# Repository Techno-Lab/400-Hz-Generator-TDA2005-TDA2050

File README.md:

# 400-Hz-Generator-TDA2005-TDA2050

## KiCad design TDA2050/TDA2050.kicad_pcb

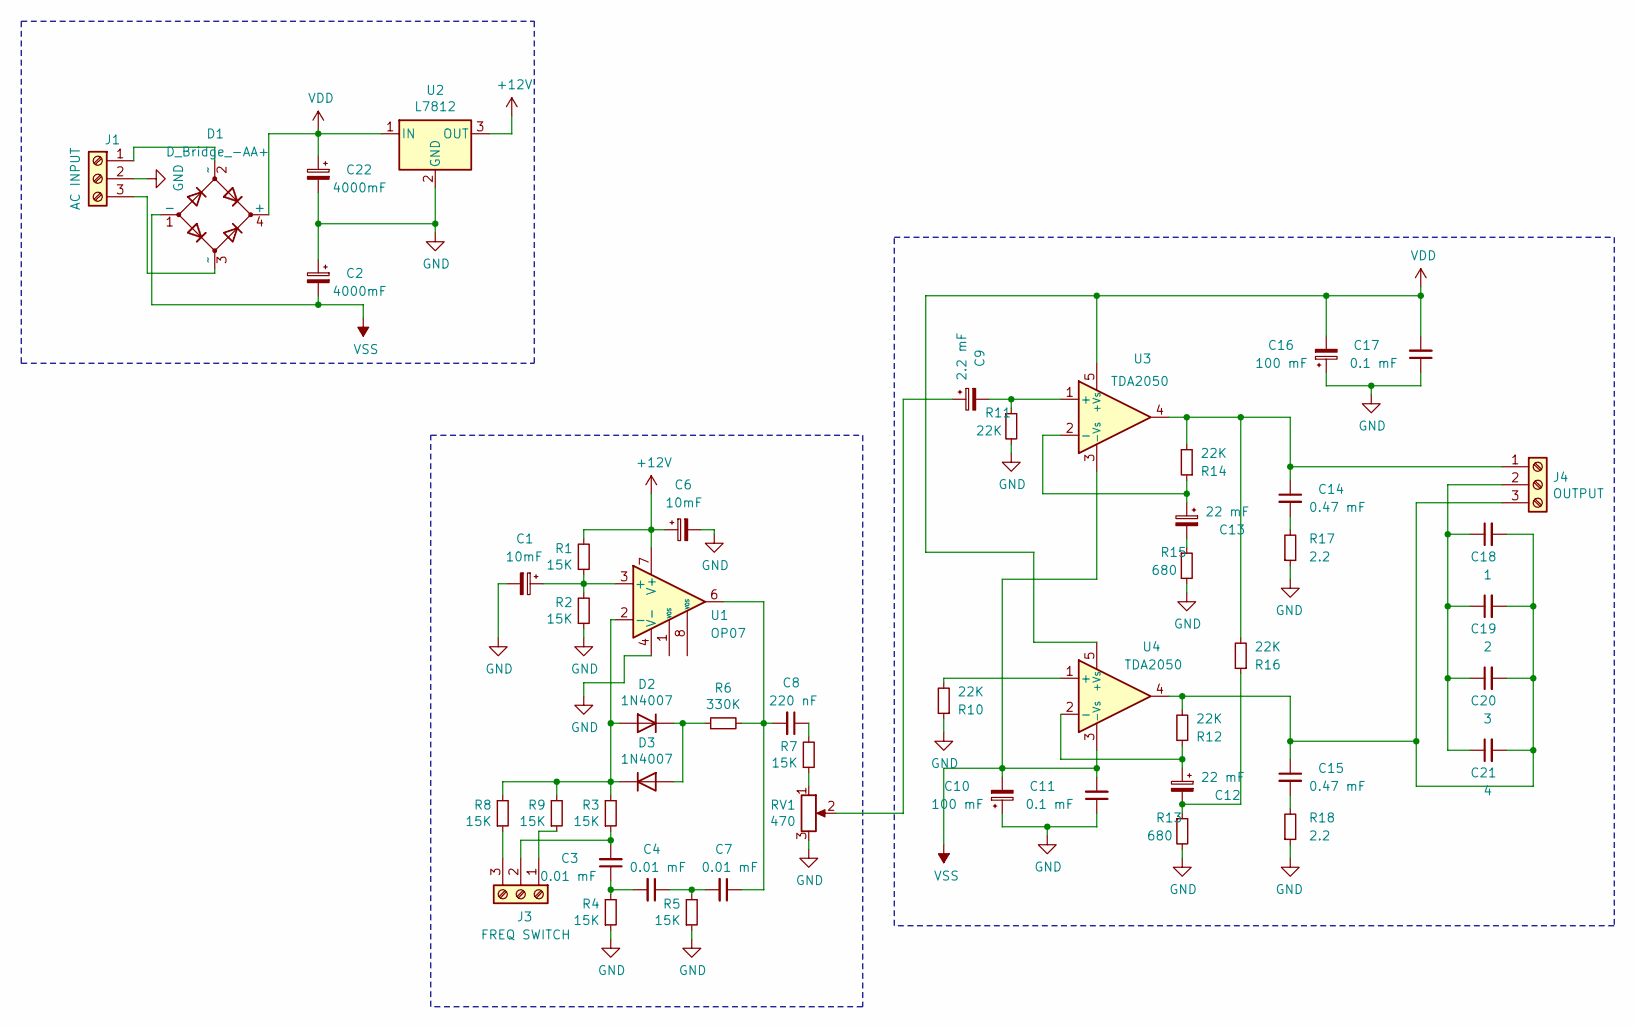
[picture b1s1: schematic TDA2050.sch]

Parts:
C1, C6: 10mF; CP_Radial_D5.0mm_P2.00mm
C2, C22: 4000mF; CP_Radial_D22.0mm_P10.00mm_SnapIn
C3, C4, C7: 0.01 mF; C_Disc_D7.5mm_W2.5mm_P5.00mm
C8: 220 nF; C_Disc_D7.5mm_W2.5mm_P5.00mm
C9: 2.2 mF; CP_Radial_D5.0mm_P2.00mm
C10, C16: 100 mF; CP_Radial_D5.0mm_P2.50mm
C11, C17: 0.1 mF; C_Disc_D7.5mm_W2.5mm_P5.00mm
C12: 22 mF; CP_Radial_D5.0mm_P2.50mm
C13: 22 mF; CP_Radial_D5.0mm_P2.00mm
C14, C15: 0.47 mF; C_Disc_D7.5mm_W2.5mm_P5.00mm
C18: 1; TerminalBlock_bornier-2_P5.08mm
C19: 2; TerminalBlock_bornier-2_P5.08mm
C20: 3; TerminalBlock_bornier-2_P5.08mm
C21: 4; TerminalBlock_bornier-2_P5.08mm
D1: D_Bridge_-AA+; Diode_Bridge_19.0x3.5x10.0mm_P5.0mm
D2, D3: 1N4007; D_DO-41_SOD81_P7.62mm_Horizontal
J1: AC INPUT; TerminalBlock_bornier-3_P5.08mm
J3: FREQ SWITCH; TerminalBlock_bornier-3_P5.08mm
J4: OUTPUT; TerminalBlock_bornier-3_P5.08mm
R1, R2, R3, R4, R5, R7, R8, R9: 15K; R_Axial_DIN0207_L6.3mm_D2.5mm_P10.16mm_Horizontal
R6: 330K; R_Axial_DIN0207_L6.3mm_D2.5mm_P10.16mm_Horizontal
R10, R11, R12, R14, R16: 22K; R_Axial_DIN0207_L6.3mm_D2.5mm_P10.16mm_Horizontal
R13, R15: 680; R_Axial_DIN0207_L6.3mm_D2.5mm_P10.16mm_Horizontal
R17, R18: 2.2; R_Axial_DIN0207_L6.3mm_D2.5mm_P10.16mm_Horizontal
RV1: 470; Potentiometer_Bourns_3296W_Vertical
U1: OP07; DIP-8_W7.62mm
U2: L7812; TO-220-3_Vertical
U3, U4: TDA2050; TO-220-5_P3.4x3.7mm_StaggerOdd_Lead3.8mm_Vertical

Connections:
+12V: C6.1, R1.2, U1.7 (V+), U2.3 (OUT)
GND: C1.2, C2.1, C6.2, C10.1, C11.1, C16.1, C17.1, C22.2, J1.2, R2.1, R4.1, R5.1, R10.1, R11.2, R13.2, R15.2, R17.1, R18.1, RV1.3, U1.4 (V-), U2.2 (GND)
unnamed: C1.1, R1.1, R2.2, U1.3 (+)
unnamed: C3.1, C4.2, R4.2
unnamed: C3.2, J3.2, R3.1
unnamed: C4.1, C7.2, R5.2
unnamed: C7.1, C8.2, R6.2, U1.6
unnamed: C8.1, R7.2
unnamed: C9.1, RV1.2
unnamed: C9.2, R11.1, U3.1 (+)
unnamed: C12.1, R12.1, U4.2 (-)
unnamed: C12.2, R13.1, R16.1
unnamed: C13.1, R14.1, U3.2 (-)
unnamed: C13.2, R15.1
unnamed: C14.1, J4.1, R14.2, R16.2, U3.4
unnamed: C14.2, R17.2
unnamed: C15.1, C18.2, C19.2, C20.2, C21.2, J4.3, R12.2, U4.4
unnamed: C15.2, R18.2
unnamed: C18.1, C19.1, C20.1, C21.1, J4.2
unnamed: D1.2 (~~), J1.1
unnamed: D1.3 (~~), J1.3
unnamed: D2.1 (K), D3.2 (A), R6.1
unnamed: D2.2 (A), D3.1 (K), R3.2, R8.2, R9.2, U1.2 (-)
unnamed: J3.1, R9.1
unnamed: J3.3, R8.1
unnamed: R7.1, RV1.1
unnamed: R10.2, U4.1 (+)
VDD: C16.2, C17.2, C22.1, D1.4 (+), U2.1 (IN), U3.5 (+Vs), U4.5 (+Vs)
VSS: C2.2, C10.2, C11.2, D1.1 (-), U3.3 (-Vs), U4.3 (-Vs)

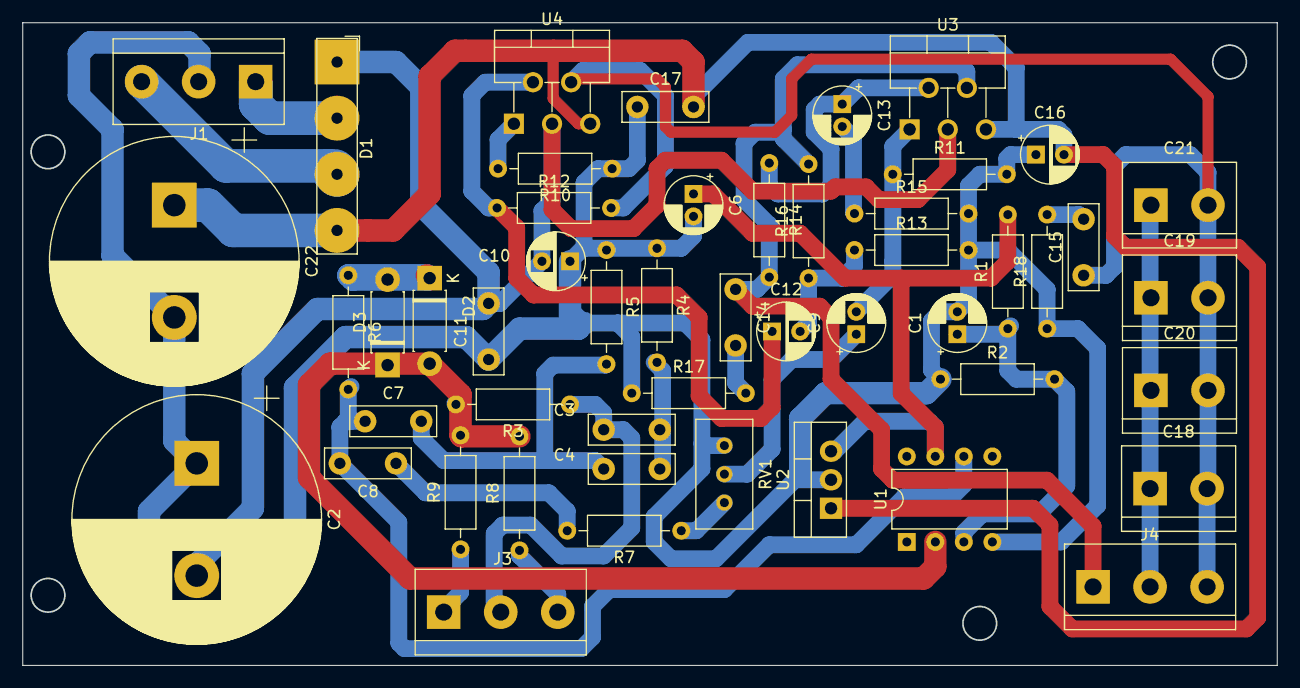
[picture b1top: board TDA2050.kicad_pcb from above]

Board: 2 copper layers, 111.7 x 57.1 mm, 50 parts (0 on the bottom side), 29 nets.

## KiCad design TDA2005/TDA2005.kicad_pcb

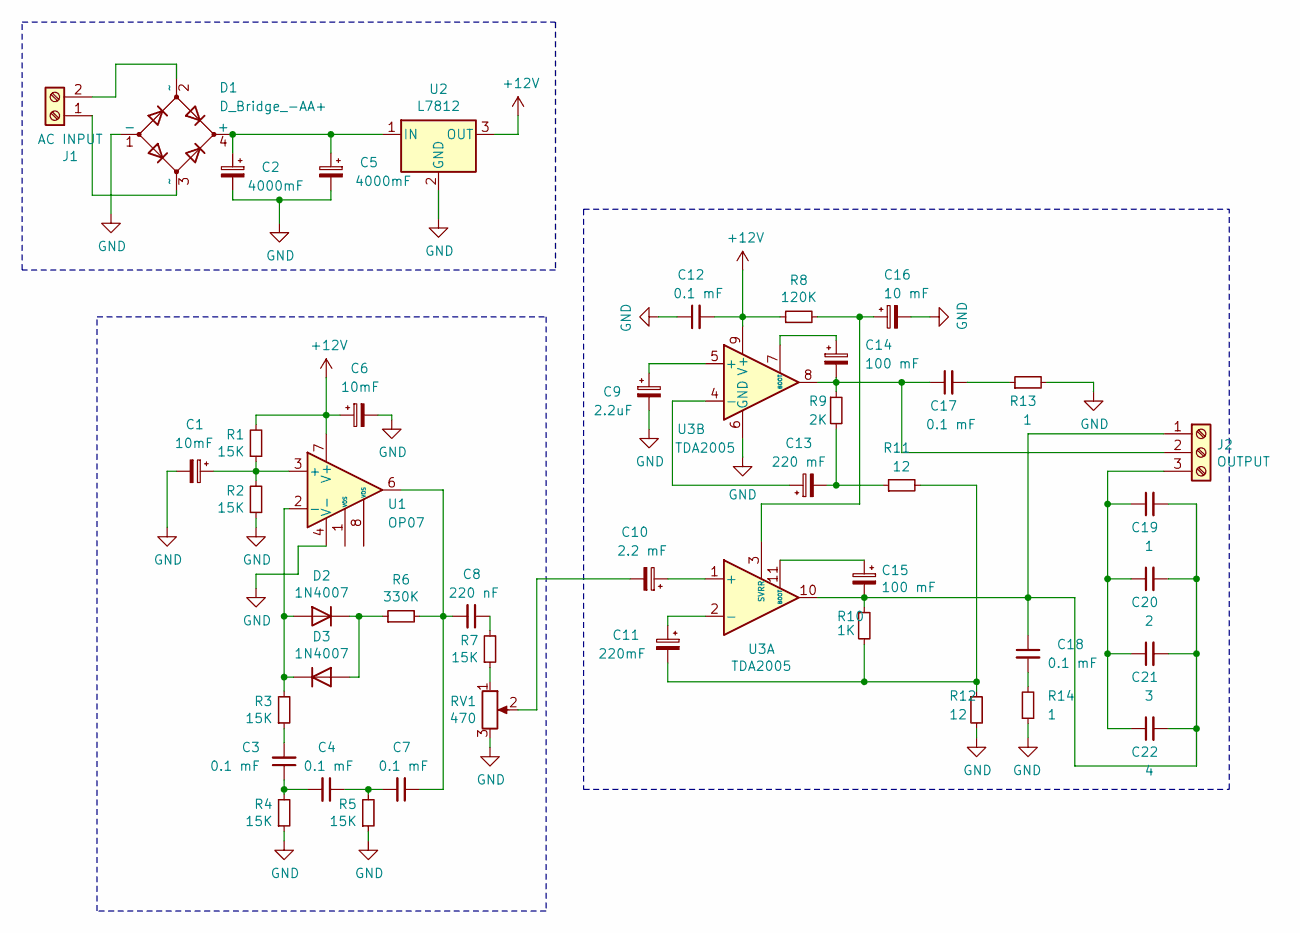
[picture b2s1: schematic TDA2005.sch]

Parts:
C1, C6: 10mF; CP_Radial_D5.0mm_P2.00mm
C2, C5: 4000mF; CP_Radial_D22.0mm_P10.00mm_SnapIn
C3, C4, C7, C12, C17, C18: 0.1 mF; C_Disc_D7.5mm_W2.5mm_P5.00mm
C8: 220 nF; C_Disc_D7.5mm_W2.5mm_P5.00mm
C9: 2.2uF; C_Disc_D7.5mm_W2.5mm_P5.00mm
C10: 2.2 mF; C_Disc_D7.5mm_W2.5mm_P5.00mm
C11: 220mF; CP_Radial_D8.0mm_P3.80mm
C13: 220 mF; CP_Radial_D8.0mm_P3.80mm
C14, C15: 100 mF; CP_Radial_D6.3mm_P2.50mm
C16: 10 mF; CP_Radial_D5.0mm_P2.00mm
C19: 1; C_Rect_L16.5mm_W4.7mm_P15.00mm_MKT
C20: 2; C_Rect_L16.5mm_W4.7mm_P15.00mm_MKT
C21: 3; C_Rect_L16.5mm_W4.7mm_P15.00mm_MKT
C22: 4; C_Rect_L16.5mm_W4.7mm_P15.00mm_MKT
D1: D_Bridge_-AA+; Diode_Bridge_19.0x3.5x10.0mm_P5.0mm
D2, D3: 1N4007; D_DO-41_SOD81_P7.62mm_Horizontal
J1: AC INPUT; TerminalBlock_bornier-2_P5.08mm
J2: OUTPUT; TerminalBlock_bornier-3_P5.08mm
R1, R2, R3, R4, R5, R7: 15K; R_Axial_DIN0207_L6.3mm_D2.5mm_P10.16mm_Horizontal
R6: 330K; R_Axial_DIN0207_L6.3mm_D2.5mm_P10.16mm_Horizontal
R8: 120K; R_Axial_DIN0207_L6.3mm_D2.5mm_P10.16mm_Horizontal
R9: 2K; R_Axial_DIN0207_L6.3mm_D2.5mm_P10.16mm_Horizontal
R10: 1K; R_Axial_DIN0207_L6.3mm_D2.5mm_P10.16mm_Horizontal
R11, R12: 12; R_Axial_DIN0207_L6.3mm_D2.5mm_P10.16mm_Horizontal
R13, R14: 1; R_Axial_DIN0411_L9.9mm_D3.6mm_P20.32mm_Horizontal
RV1: 470; Potentiometer_Bourns_3296W_Vertical
U1: OP07; DIP-8_W7.62mm
U2: L7812; TO-220-3_Vertical
U3: TDA2005; TO-220-11_P3.4x5.08mm_StaggerOdd_Lead4.85mm_Vertical

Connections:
+12V: C6.1, C12.2, R1.2, R8.1, U1.7 (V+), U2.3 (OUT), U3.9 (V+)
GND: C1.2, C2.2, C5.2, C6.2, C9.2, C12.1, C16.2, D1.1 (-), R2.1, R4.1, R5.1, R12.2, R13.2, R14.1, RV1.3, U1.4 (V-), U2.2 (GND), U3.6 (GND)
unnamed: C1.1, R1.1, R2.2, U1.3 (+)
unnamed: C2.1, C5.1, D1.4 (+), U2.1 (IN)
unnamed: C3.1, C4.2, R4.2
unnamed: C3.2, R3.1
unnamed: C4.1, C7.2, R5.2
unnamed: C7.1, C8.2, R6.2, U1.6
unnamed: C8.1, R7.2
unnamed: C9.1, U3.5 (+)
unnamed: C10.1, U3.1 (+)
unnamed: C10.2, RV1.2
unnamed: C11.1, U3.2 (-)
unnamed: C11.2, R10.2, R11.2, R12.1
unnamed: C13.1, U3.4 (-)
unnamed: C13.2, R9.2, R11.1
unnamed: C14.1, U3.7 (BOOT)
unnamed: C14.2, C17.1, J2.2, R9.1, U3.8
unnamed: C15.1, U3.11 (BOOT)
unnamed: C15.2, C18.1, C19.2, C20.2, C21.2, C22.2, J2.1, R10.1, U3.10
unnamed: C16.1, R8.2, U3.3 (SVRR)
unnamed: C17.2, R13.1
unnamed: C18.2, R14.2
unnamed: C19.1, C20.1, C21.1, C22.1, J2.3
unnamed: D1.2 (~~), J1.2
unnamed: D1.3 (~~), J1.1
unnamed: D2.1 (K), D3.2 (A), R6.1
unnamed: D2.2 (A), D3.1 (K), R3.2, U1.2 (-)
unnamed: R7.1, RV1.1

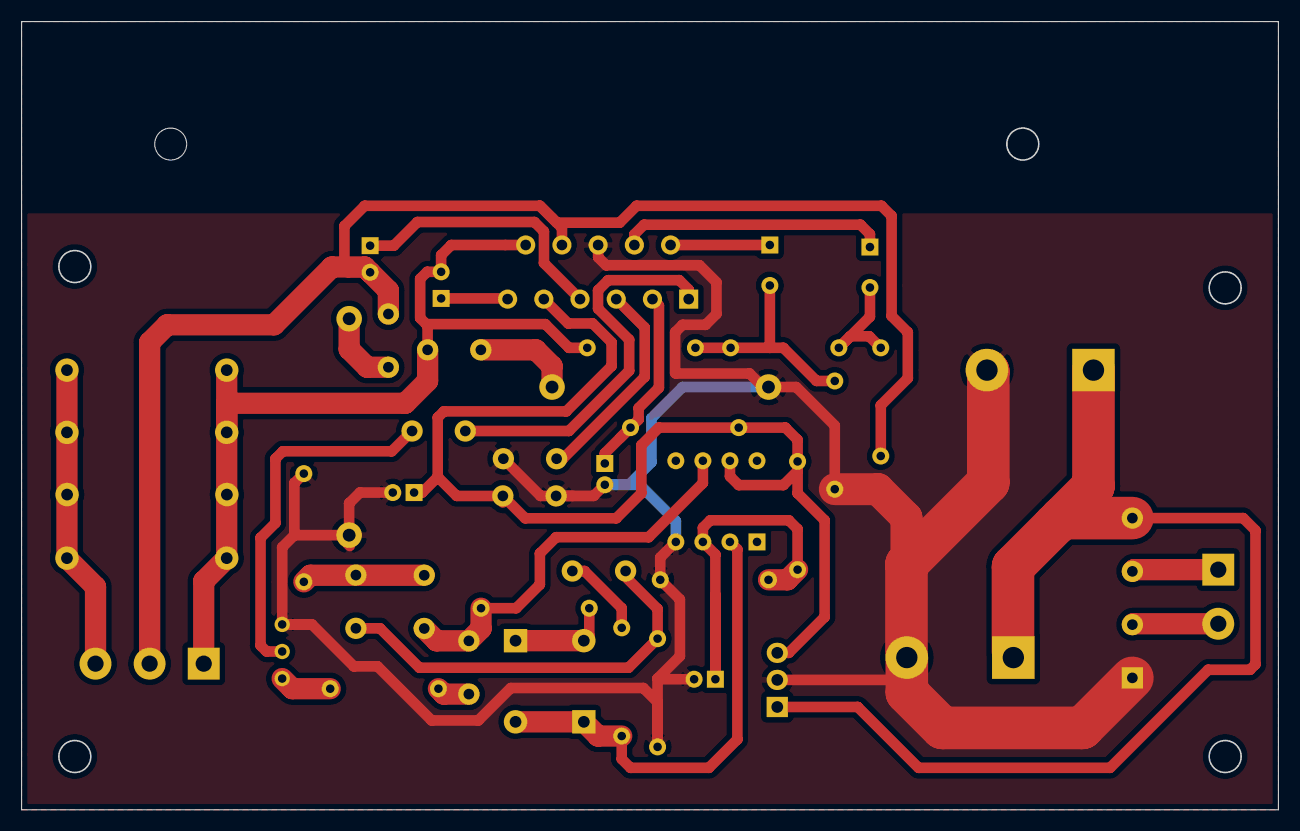
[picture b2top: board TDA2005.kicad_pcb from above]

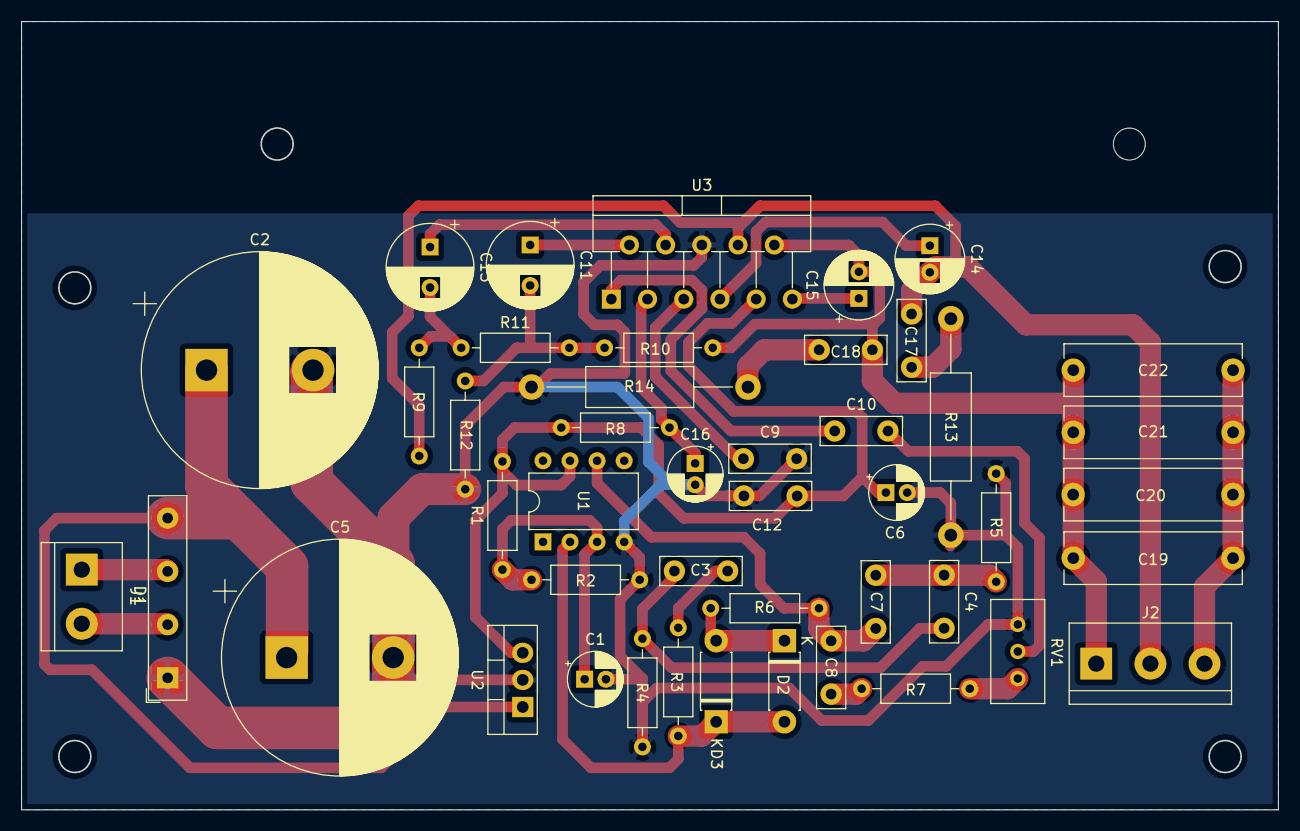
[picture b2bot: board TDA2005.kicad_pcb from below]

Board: 2 copper layers, 117.9 x 73.9 mm, 45 parts (45 on the bottom side), 29 nets.

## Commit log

2021-11-12 Added TDA2005 PCB and SCHEMATIC
2021-11-12 Added TDA2050 PCB and SCHEMATIC
